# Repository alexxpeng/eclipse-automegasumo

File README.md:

# eclipse-automegasumo
Eclipse - 3kg Autonomous Mega Sumo

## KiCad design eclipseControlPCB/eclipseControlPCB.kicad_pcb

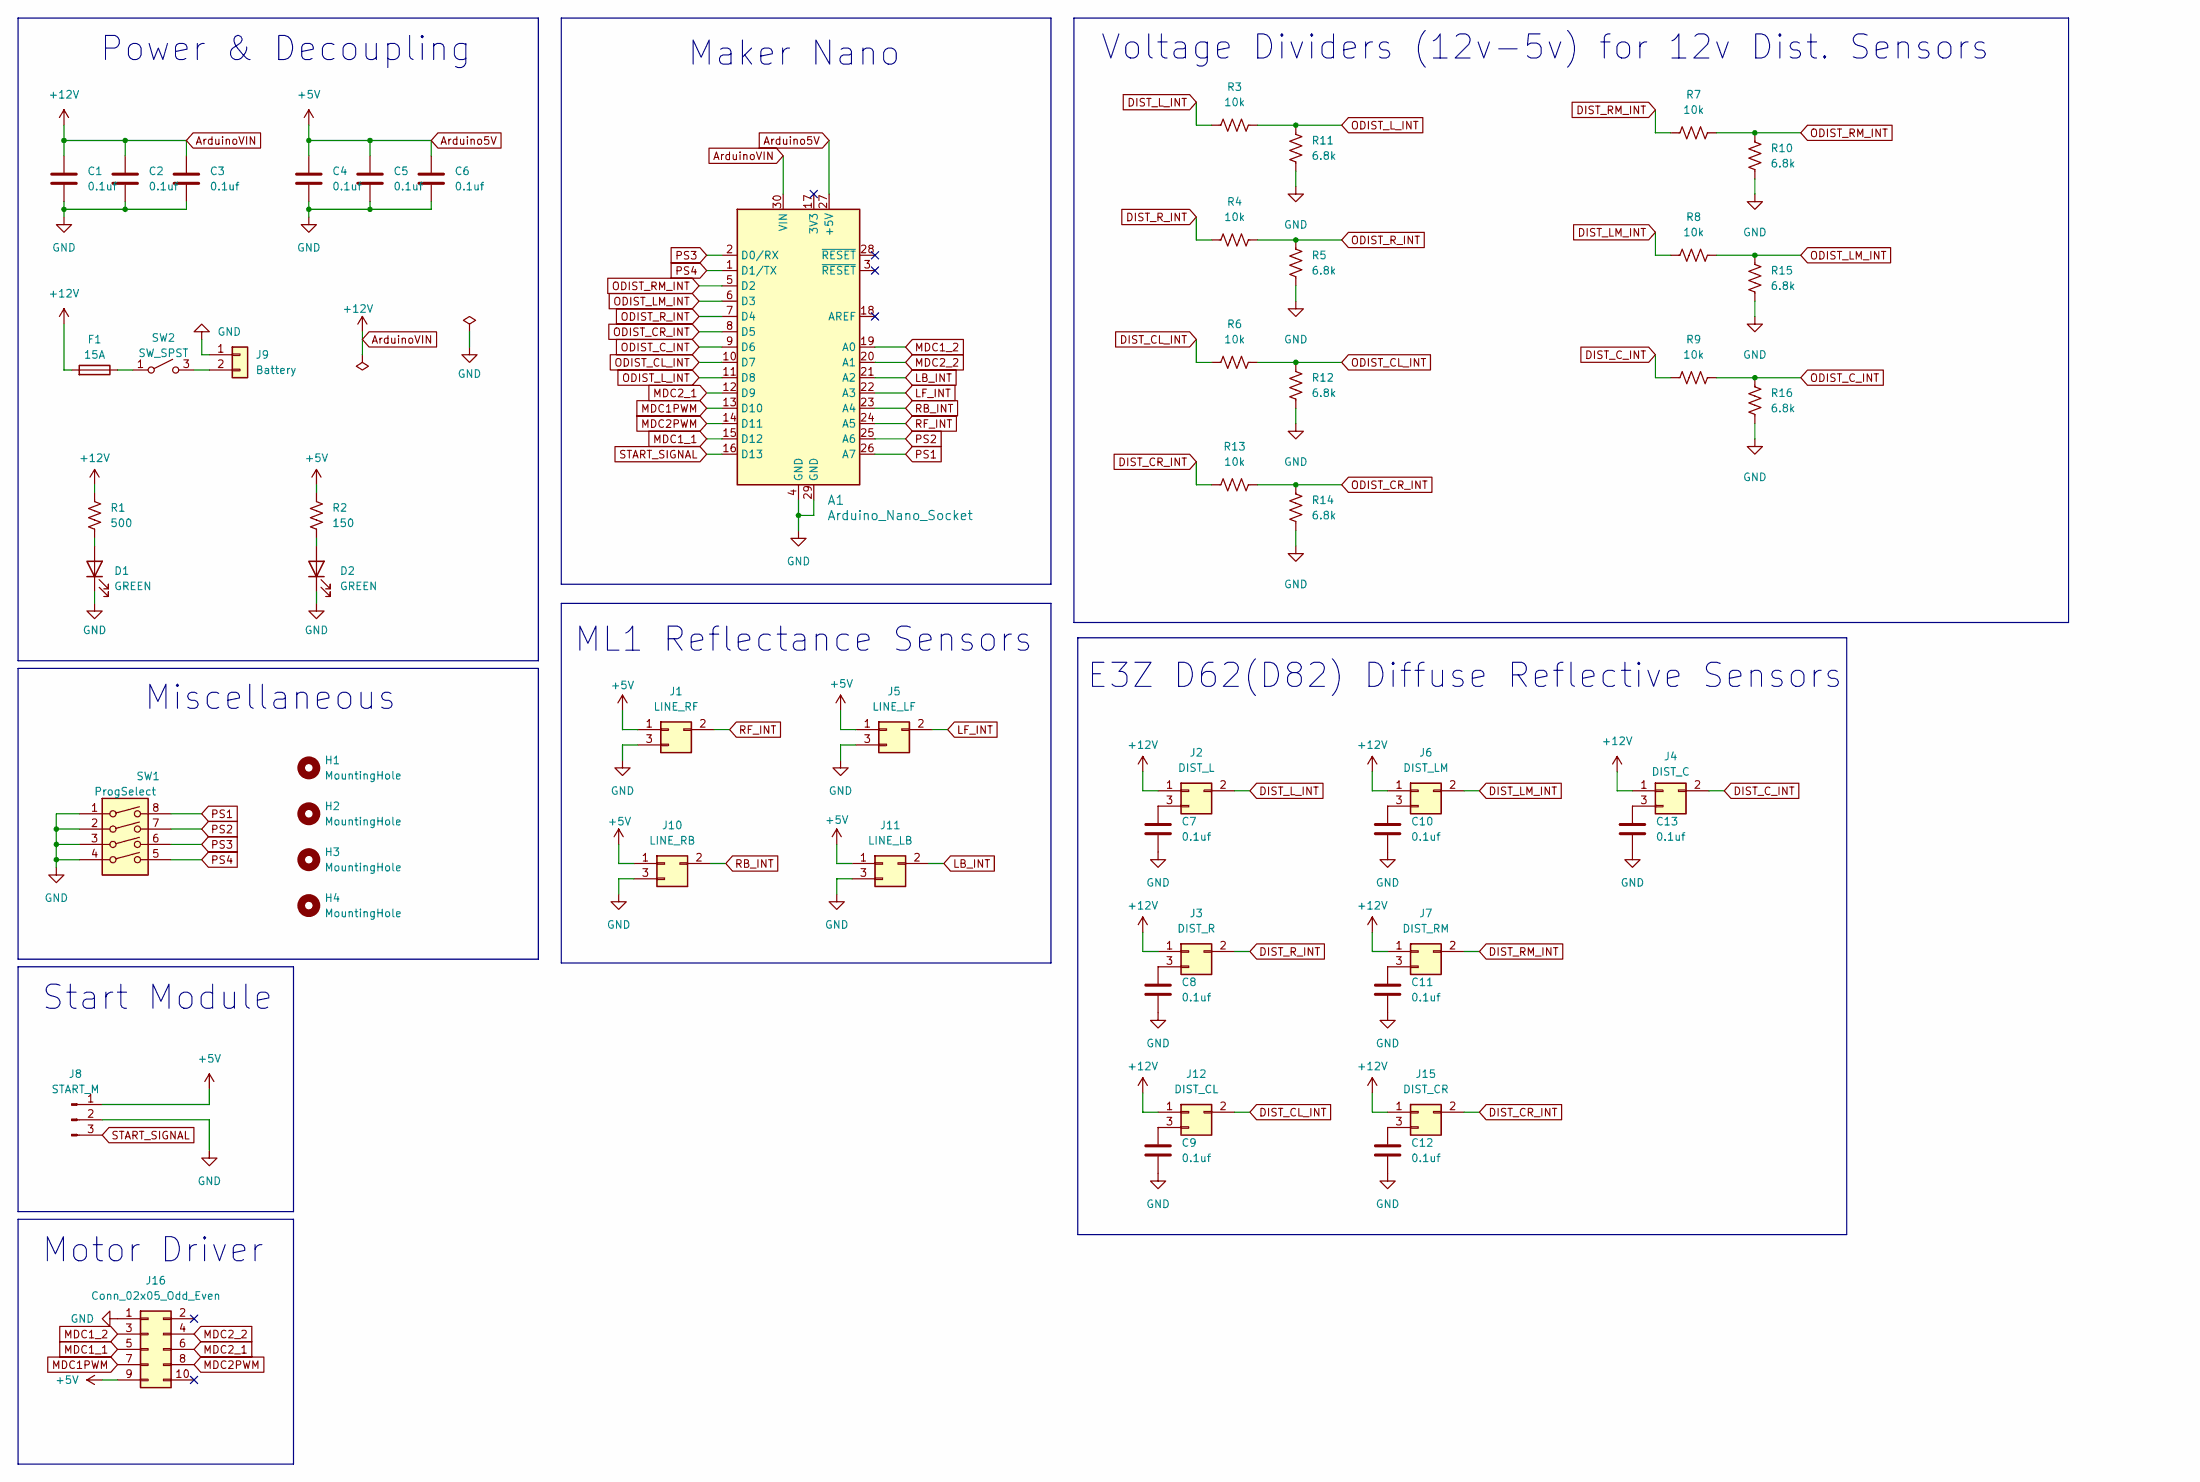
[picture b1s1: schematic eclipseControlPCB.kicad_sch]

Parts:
A1: Arduino_Nano_Socket; Arduino_Nano
C1, C2, C3, C4, C5, C6, C7, C8, C9, C10, C11, C12, C13: 0.1uf; C_0805_2012Metric_Pad1.18x1.45mm_HandSolder
D1, D2: GREEN; C_0603_1608Metric_Pad1.08x0.95mm_HandSolder
F1: 15A; Fuse_1206_3216Metric_Pad1.42x1.75mm_HandSolder
H1, H2, H3, H4: MountingHole; MountingHole_2.2mm_M2_ISO7380
J1: LINE_RF; PinHeader_1x03_P2.54mm_Vertical
J2: DIST_L; PinHeader_1x03_P2.54mm_Vertical
J3: DIST_R; PinHeader_1x03_P2.54mm_Vertical
J4: DIST_C; PinHeader_1x03_P2.54mm_Vertical
J5: LINE_LF; PinHeader_1x03_P2.54mm_Vertical
J6: DIST_LM; PinHeader_1x03_P2.54mm_Vertical
J7: DIST_RM; PinHeader_1x03_P2.54mm_Vertical
J8: START_M; PinSocket_1x03_P2.54mm_Vertical
J9: Battery; TerminalBlock_Altech_AK300-2_P5.00mm
J10: LINE_RB; PinHeader_1x03_P2.54mm_Vertical
J11: LINE_LB; PinHeader_1x03_P2.54mm_Vertical
J12: DIST_CL; PinHeader_1x03_P2.54mm_Vertical
J15: DIST_CR; PinHeader_1x03_P2.54mm_Vertical
J16: Conn_02x05_Odd_Even; PinSocket_2x05_P2.54mm_Vertical
R1: 500; D_0805_2012Metric_Pad1.15x1.40mm_HandSolder
R2: 150; D_0805_2012Metric_Pad1.15x1.40mm_HandSolder
R3, R4, R6, R7, R8, R9, R13: 10k; R_0805_2012Metric_Pad1.20x1.40mm_HandSolder
R5, R10, R11, R12, R14, R15, R16: 6.8k; R_0805_2012Metric_Pad1.20x1.40mm_HandSolder
SW1: ProgSelect; SW_DIP_SPSTx04_Slide_6.7x11.72mm_W6.73mm_P2.54mm_LowProfile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
SW2: SW_SPST; SW_AS11CP

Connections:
Arduino5V: A1.27 (+5V), C4.1, C5.1, C6.1, J1.1, J5.1, J8.1, J10.1, J11.1, J16.9, R2.1
ArduinoVIN: A1.30 (VIN), C1.1, C2.1, C3.1, F1.2, J2.1, J3.1, J4.1, J6.1, J7.1, J12.1, J15.1, R1.1
DIST_CL_INT: J12.2, R6.1
DIST_CR_INT: J15.2, R13.1
DIST_C_INT: J4.2, R9.1
DIST_LM_INT: J6.2, R8.1
DIST_L_INT: J2.2, R3.1
DIST_RM_INT: J7.2, R7.1
DIST_R_INT: J3.2, R4.1
GND: A1.4 (GND), A1.29 (GND), C1.2, C2.2, C3.2, C4.2, C5.2, C6.2, C7.2, C8.2, C9.2, C10.2, C11.2, C12.2, C13.2, D1.1 (K), D2.1 (K), J1.3, J5.3, J8.2, J9.1, J10.3, J11.3, J16.1, R5.1, R10.1, R11.1, R12.1, R14.1, R15.1, R16.1, SW1.1, SW1.2, SW1.3, SW1.4
LB_INT: A1.21 (A2), J11.2
LF_INT: A1.22 (A3), J5.2
MDC1PWM: A1.13 (D10), J16.7
MDC1_1: A1.15 (D12), J16.5
MDC1_2: A1.19 (A0), J16.3
MDC2PWM: A1.14 (D11), J16.8
MDC2_1: A1.12 (D9), J16.6
MDC2_2: A1.20 (A1), J16.4
unnamed: D1.2 (A), R1.2
unnamed: D2.2 (A), R2.2
unnamed: C7.1, J2.3
unnamed: C8.1, J3.3
unnamed: C13.1, J4.3
unnamed: C10.1, J6.3
unnamed: C11.1, J7.3
unnamed: J9.2, SW2.3 (B)
unnamed: C9.1, J12.3
unnamed: C12.1, J15.3
unnamed: F1.1, SW2.1 (A)
ODIST_CL_INT: A1.10 (D7), R6.2, R12.2
ODIST_CR_INT: A1.8 (D5), R13.2, R14.2
ODIST_C_INT: A1.9 (D6), R9.2, R16.2
ODIST_LM_INT: A1.6 (D3), R8.2, R15.2
ODIST_L_INT: A1.11 (D8), R3.2, R11.2
ODIST_RM_INT: A1.5 (D2), R7.2, R10.2
ODIST_R_INT: A1.7 (D4), R4.2, R5.2
PS1: A1.26 (A7), SW1.8
PS2: A1.25 (A6), SW1.7
PS3: A1.2 (D0/RX), SW1.6
PS4: A1.1 (D1/TX), SW1.5
RB_INT: A1.23 (A4), J10.2
RF_INT: A1.24 (A5), J1.2
START_SIGNAL: A1.16 (D13), J8.3

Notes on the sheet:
E3Z D62(D82) Diffuse Reflective Sensors
Motor Driver
Maker Nano
Start Module
Power & Decoupling
ML1 Reflectance Sensors
Miscellaneous
Voltage Dividers (12v-5v) for 12v Dist. Sensors

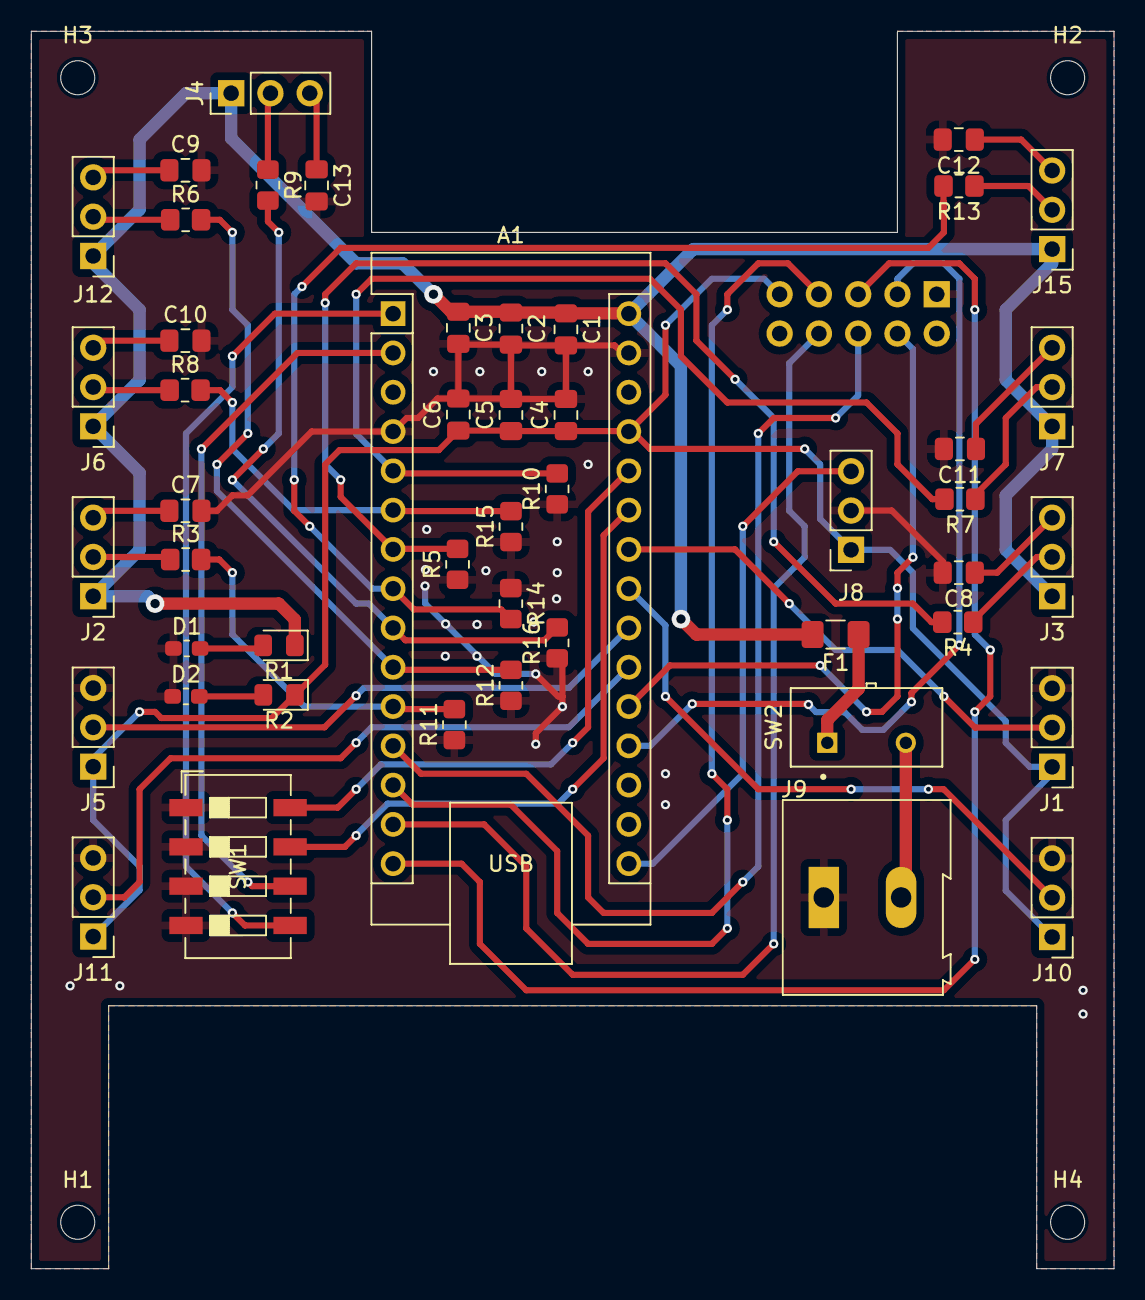
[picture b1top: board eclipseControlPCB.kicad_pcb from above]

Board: 2 copper layers, 70.0 x 80.0 mm, 53 parts (1 on the bottom side), 43 nets.

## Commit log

2024-12-22 Schematic w/ Optocoupler
    gnd not isolated, need dc-dc converter isolator for arduino vin and gnd for ideal functionality
2025-01-15 no optocoupler implementation
    board layout designed to stack on aliexpress motor driver
2025-01-21 updated layout dimensions
    compatible (stackable) with aliexpress motor driver
